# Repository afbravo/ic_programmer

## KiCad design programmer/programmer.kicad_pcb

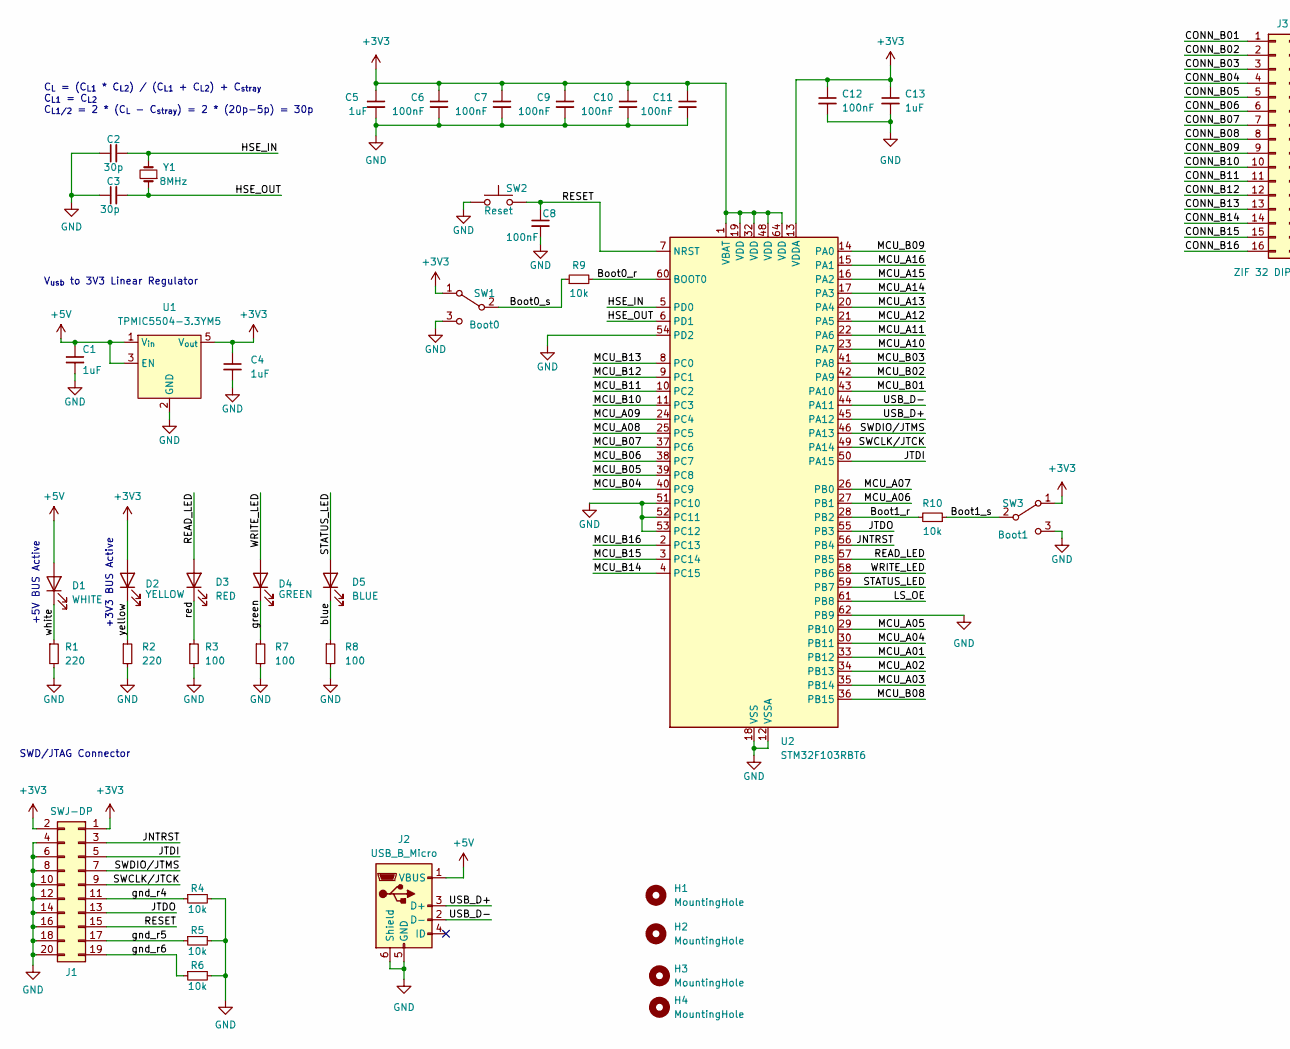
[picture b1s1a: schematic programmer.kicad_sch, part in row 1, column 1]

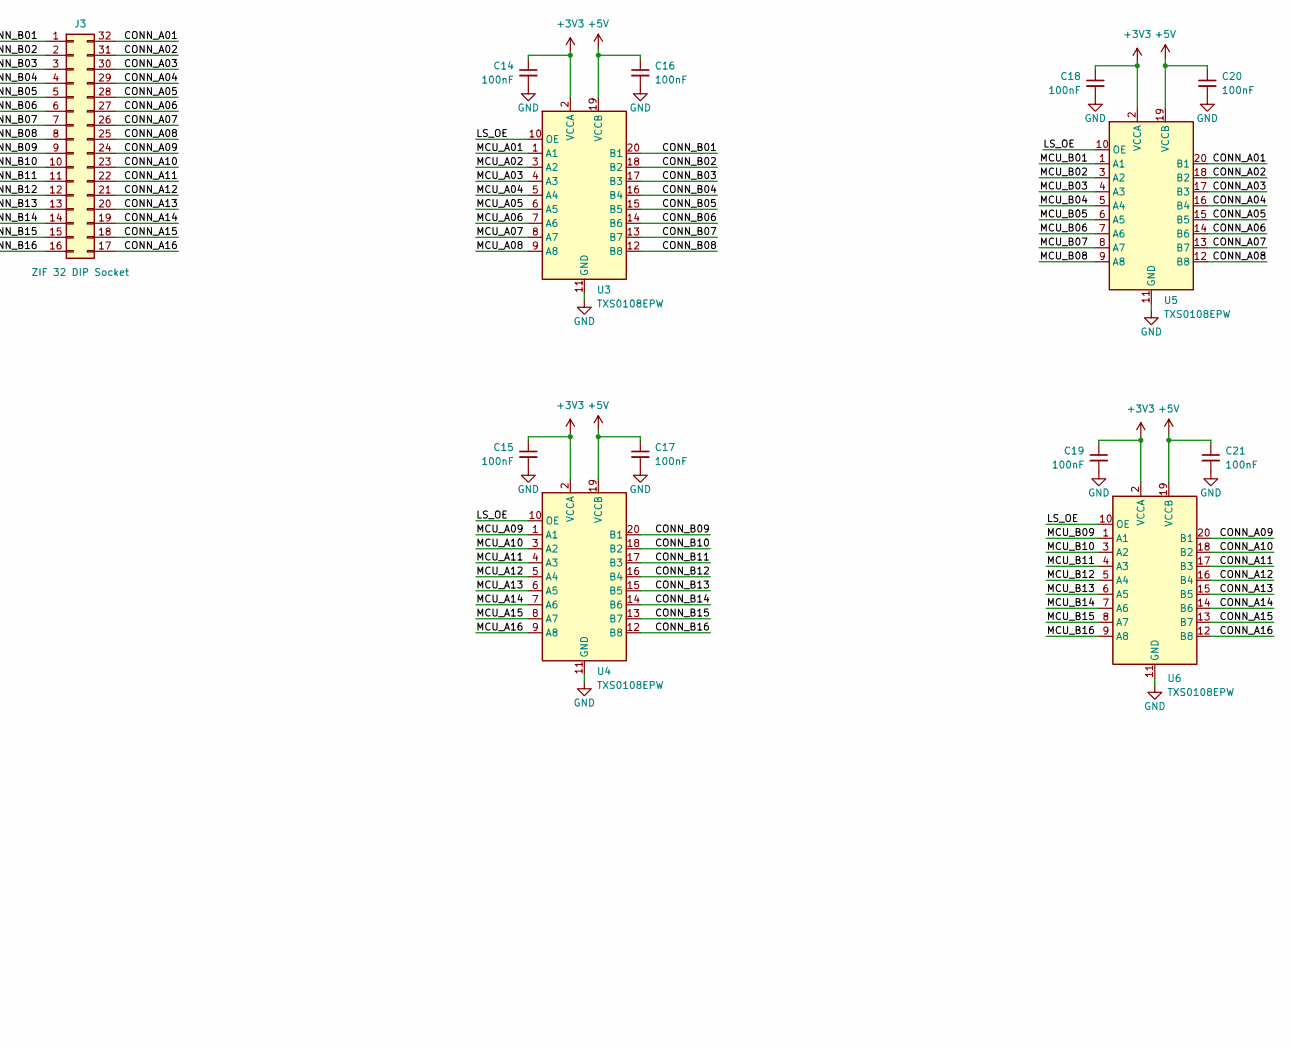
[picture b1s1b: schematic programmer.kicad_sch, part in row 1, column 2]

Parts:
C1, C4, C5, C13: 1uF; C_0603_1608Metric; LCSC C93816
C2, C3: 30p; C_0402_1005Metric; LCSC C525209
C6, C7, C8, C9, C10, C11, C12, C14, C15, C16, C17, C18, C19, C20, C21: 100nF; C_0402_1005Metric; LCSC C71629
D1: WHITE; LED_0805_2012Metric; LCSC C34499
D2: YELLOW; LED_0805_2012Metric; LCSC C434434
D3: RED; LED_0805_2012Metric; LCSC C84256
D4: GREEN; LED_0805_2012Metric; LCSC C2297
D5: BLUE; LED_0805_2012Metric; LCSC C84259
H1, H2, H3, H4: MountingHole; MountingHole_3.2mm_M3_Pad_Via
J1: SWJ-DP; PinHeader_2x10_P2.54mm_Vertical; LCSC C3405
J2: USB_B_Micro; USB_Micro-B_XKB_U254-051T-4BH83-F1S; LCSC C2682229
J3: ZIF 32 DIP Socket; DIP_Socket-32_W11.9_W12.7_W15.24_W17.78_W18.5_3M_232-1285-0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
R1, R2: 220; R_0402_1005Metric; LCSC C102898
R3, R7, R8: 100; R_0402_1005Metric; LCSC C106233
R4, R5, R6, R9, R10: 10k; R_0603_1608Metric; LCSC C190610
SW1: Boot0; SW_SWDT_SMD_0.8x1.4_0.8x2; LCSC C319019
SW2: Reset; SW_SMD_1.8x1.35_4.15; LCSC C720477
SW3: Boot1; SW_SWDT_SMD_0.8x1.4_0.8x2; LCSC C319019
U1: TPMIC5504-3.3YM5; SOT-23-5; LCSC C3021093
U2: STM32F103RBT6; LQFP-64_10x10mm_P0.5mm; LCSC C8735
U3, U4, U5, U6: TXS0108EPW; TSSOP-20_4.4x6.5mm_P0.65mm
Y1: 8MHz; Crystal_SMD_5032-2Pin_5.0x3.2mm; LCSC C115962

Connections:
+3V3: C4.1, C5.1, C6.1, C7.1, C9.1, C10.1, C11.1, C12.1, C13.1, C14.1, C15.1, C18.1, C19.1, D2.2 (A), J1.1, J1.2, SW1.1 (A), SW3.1 (A), U1.5 (V_{out}), U2.1 (VBAT), U2.13 (VDDA), U2.19 (VDD), U2.32 (VDD), U2.48 (VDD), U2.64 (VDD), U3.2 (VCCA), U4.2 (VCCA), U5.2 (VCCA), U6.2 (VCCA)
+5V: C1.1, C16.1, C17.1, C20.1, C21.1, D1.2 (A), J2.1 (VBUS), U1.1 (V_{in}), U1.3 (EN), U3.19 (VCCB), U4.19 (VCCB), U5.19 (VCCB), U6.19 (VCCB)
/Boot0_r: R9.2, U2.60 (BOOT0)
/Boot0_s: R9.1, SW1.2 (B)
/Boot1_r: R10.2, U2.28 (PB2)
/Boot1_s: R10.1, SW3.2 (B)
/CONN_A01: J3.32, U5.20 (B1)
/CONN_A02: J3.31, U5.18 (B2)
/CONN_A03: J3.30, U5.17 (B3)
/CONN_A04: J3.29, U5.16 (B4)
/CONN_A05: J3.28, U5.15 (B5)
/CONN_A06: J3.27, U5.14 (B6)
/CONN_A07: J3.26, U5.13 (B7)
/CONN_A08: J3.25, U5.12 (B8)
/CONN_A09: J3.24, U6.20 (B1)
/CONN_A10: J3.23, U6.18 (B2)
/CONN_A11: J3.22, U6.17 (B3)
/CONN_A12: J3.21, U6.16 (B4)
/CONN_A13: J3.20, U6.15 (B5)
/CONN_A14: J3.19, U6.14 (B6)
/CONN_A15: J3.18, U6.13 (B7)
/CONN_A16: J3.17, U6.12 (B8)
/CONN_B01: J3.1, U3.20 (B1)
/CONN_B02: J3.2, U3.18 (B2)
/CONN_B03: J3.3, U3.17 (B3)
/CONN_B04: J3.4, U3.16 (B4)
/CONN_B05: J3.5, U3.15 (B5)
/CONN_B06: J3.6, U3.14 (B6)
/CONN_B07: J3.7, U3.13 (B7)
/CONN_B08: J3.8, U3.12 (B8)
/CONN_B09: J3.9, U4.20 (B1)
/CONN_B10: J3.10, U4.18 (B2)
/CONN_B11: J3.11, U4.17 (B3)
/CONN_B12: J3.12, U4.16 (B4)
/CONN_B13: J3.13, U4.15 (B5)
/CONN_B14: J3.14, U4.14 (B6)
/CONN_B15: J3.15, U4.13 (B7)
/CONN_B16: J3.16, U4.12 (B8)
/HSE_IN: C2.2, U2.5 (PD0), Y1.2
/HSE_OUT: C3.2, U2.6 (PD1), Y1.1
/JNTRST: J1.3, U2.56 (PB4)
/JTDI: J1.5, U2.50 (PA15)
/JTDO: J1.13, U2.55 (PB3)
/LS_OE: U2.61 (PB8), U3.10 (OE), U4.10 (OE), U5.10 (OE), U6.10 (OE)
/MCU_A01: U2.33 (PB12), U3.1 (A1)
/MCU_A02: U2.34 (PB13), U3.3 (A2)
/MCU_A03: U2.35 (PB14), U3.4 (A3)
/MCU_A04: U2.30 (PB11), U3.5 (A4)
/MCU_A05: U2.29 (PB10), U3.6 (A5)
/MCU_A06: U2.27 (PB1), U3.7 (A6)
/MCU_A07: U2.26 (PB0), U3.8 (A7)
/MCU_A08: U2.25 (PC5), U3.9 (A8)
/MCU_A09: U2.24 (PC4), U4.1 (A1)
/MCU_A10: U2.23 (PA7), U4.3 (A2)
/MCU_A11: U2.22 (PA6), U4.4 (A3)
/MCU_A12: U2.21 (PA5), U4.5 (A4)
/MCU_A13: U2.20 (PA4), U4.6 (A5)
/MCU_A14: U2.17 (PA3), U4.7 (A6)
/MCU_A15: U2.16 (PA2), U4.8 (A7)
/MCU_A16: U2.15 (PA1), U4.9 (A8)
/MCU_B01: U2.43 (PA10), U5.1 (A1)
/MCU_B02: U2.42 (PA9), U5.3 (A2)
/MCU_B03: U2.41 (PA8), U5.4 (A3)
/MCU_B04: U2.40 (PC9), U5.5 (A4)
/MCU_B05: U2.39 (PC8), U5.6 (A5)
/MCU_B06: U2.38 (PC7), U5.7 (A6)
/MCU_B07: U2.37 (PC6), U5.8 (A7)
/MCU_B08: U2.36 (PB15), U5.9 (A8)
/MCU_B09: U2.14 (PA0), U6.1 (A1)
/MCU_B10: U2.11 (PC3), U6.3 (A2)
/MCU_B11: U2.10 (PC2), U6.4 (A3)
/MCU_B12: U2.9 (PC1), U6.5 (A4)
/MCU_B13: U2.8 (PC0), U6.6 (A5)
/MCU_B14: U2.4 (PC15), U6.7 (A6)
/MCU_B15: U2.3 (PC14), U6.8 (A7)
/MCU_B16: U2.2 (PC13), U6.9 (A8)
/READ_LED: D3.2 (A), U2.57 (PB5)
/RESET: C8.1, J1.15, SW2.2, U2.7 (NRST)
/STATUS_LED: D5.2 (A), U2.59 (PB7)
/SWCLK/JTCK: J1.9, U2.49 (PA14)
/SWDIO/JTMS: J1.7, U2.46 (PA13)
/USB_D+: J2.3 (D+), U2.45 (PA12)
/USB_D-: J2.2 (D-), U2.44 (PA11)
/WRITE_LED: D4.2 (A), U2.58 (PB6)
/blue: D5.1 (K), R8.1
/gnd_r4: J1.11, R4.1
/gnd_r5: J1.17, R5.1
/gnd_r6: J1.19, R6.1
/green: D4.1 (K), R7.1
/red: D3.1 (K), R3.1
/white: D1.1 (K), R1.1
/yellow: D2.1 (K), R2.1
GND: C1.2, C2.1, C3.1, C4.2, C5.2, C6.2, C7.2, C8.2, C9.2, C10.2, C11.2, C12.2, C13.2, C14.2, C15.2, C16.2, C17.2, C18.2, C19.2, C20.2, C21.2, J1.4, J1.6, J1.8, J1.10, J1.12, J1.14, J1.16, J1.18, J1.20, J2.5 (GND), J2.6 (Shield), R1.2, R2.2, R3.2, R4.2, R5.2, R6.2, R7.2, R8.2, SW1.3 (C), SW2.1, SW3.3 (C), U1.2 (GND), U2.12 (VSSA), U2.18 (VSS), U2.31 (VSS), U2.47 (VSS), U2.51 (PC10), U2.52 (PC11), U2.53 (PC12), U2.54 (PD2), U2.62 (PB9), U2.63 (VSS), U3.11 (GND), U4.11 (GND), U5.11 (GND), U6.11 (GND)

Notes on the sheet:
V_{usb} to 3V3 Linear Regulator
+5V BUS Active
C_{L} = (C_{L1} * C_{L2}) / (C_{L1} + C_{L2}) + C_{stray} C_{L1} = C_{L2} C_{L1/2} = 2 * (C_{L} - C_{stray}) = 2 * (20p-5p) = 30p
+3V3 BUS Active
SWD/JTAG Connector

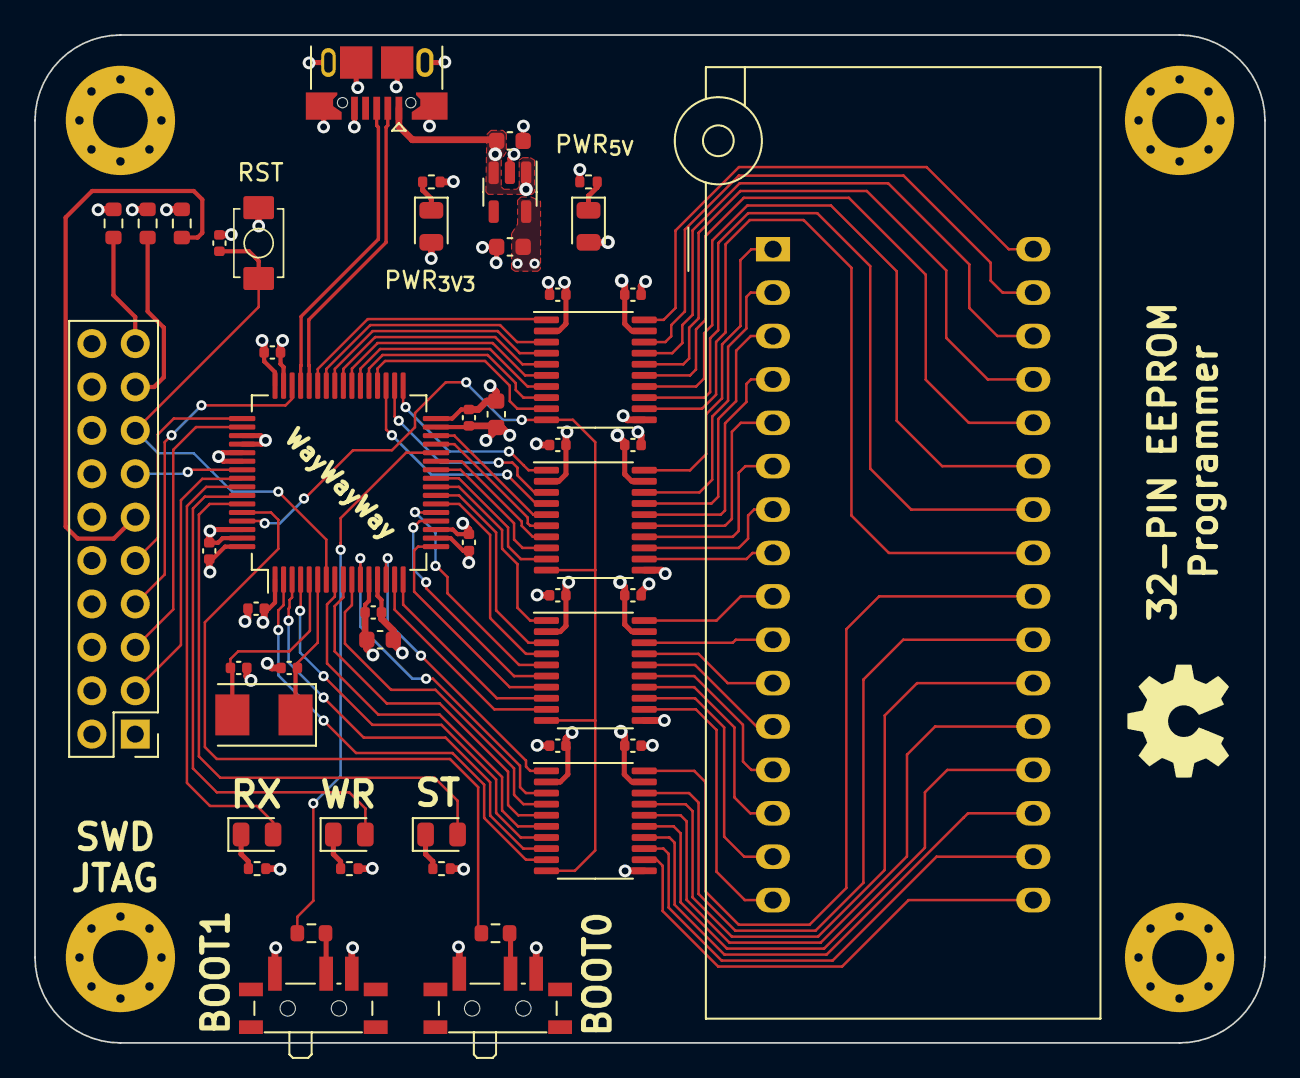
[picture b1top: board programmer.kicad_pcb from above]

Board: 4 copper layers, 72.0 x 59.0 mm, 53 parts (0 on the bottom side), 93 nets.

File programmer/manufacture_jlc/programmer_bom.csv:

Designator,Val,Package,Mid X,Mid Y,Rotation,Layer
C1,1uF,C_0603_1608Metric,138.707500,-78.620000,0.000000,top
C2,30p,C_0402_1005Metric,122.827500,-109.470000,180.000000,top
C3,30p,C_0402_1005Metric,125.787500,-109.470000,0.000000,top
C4,1uF,C_0603_1608Metric,138.707500,-84.820000,180.000000,top
C5,1uF,C_0603_1608Metric,137.907500,-94.620000,-90.000000,top
C6,100nF,C_0402_1005Metric,124.800000,-91.000000,0.000000,top
C7,100nF,C_0402_1005Metric,123.850000,-106.000000,180.000000,top
C8,100nF,C_0402_1005Metric,121.700000,-84.600000,90.000000,top
C9,100nF,C_0402_1005Metric,136.307500,-94.820000,-90.000000,top
C10,100nF,C_0402_1005Metric,121.107500,-102.620000,90.000000,top
C11,100nF,C_0402_1005Metric,136.307500,-102.120000,-90.000000,top
C12,100nF,C_0402_1005Metric,130.707500,-106.220000,180.000000,top
C13,1uF,C_0603_1608Metric,131.107500,-107.820000,180.000000,top
C14,100nF,C_0402_1005Metric,141.507500,-96.420000,180.000000,top
C15,100nF,C_0402_1005Metric,141.507500,-105.220000,180.000000,top
C16,100nF,C_0402_1005Metric,145.907500,-96.420000,0.000000,top
C17,100nF,C_0402_1005Metric,145.907500,-105.220000,0.000000,top
C18,100nF,C_0402_1005Metric,141.507500,-87.620000,180.000000,top
C19,100nF,C_0402_1005Metric,141.507500,-114.020000,180.000000,top
C20,100nF,C_0402_1005Metric,145.907500,-87.620000,0.000000,top
C21,100nF,C_0402_1005Metric,145.907500,-114.020000,0.000000,top
D1,WHITE,LED_0805_2012Metric,143.307500,-83.620000,-90.000000,top
D2,YELLOW,LED_0805_2012Metric,134.107500,-83.620000,-90.000000,top
D3,RED,LED_0805_2012Metric,123.907500,-119.220000,0.000000,top
D4,GREEN,LED_0805_2012Metric,129.307500,-119.220000,0.000000,top
D5,BLUE,LED_0805_2012Metric,134.707500,-119.220000,0.000000,top
J1,SWJ-DP,PinHeader_2x10_P2.54mm_Vertical,116.775000,-113.345000,180.000000,top
J2,USB_B_Micro,USB_Micro-B_XKB_U254-051T-4BH83-F1S,130.907500,-74.420000,180.000000,top
J3,ZIF 32 DIP Socket,DIP_Socket-32_W11.9_W12.7_W15.24_W17.78_W18.5_3M_232-1285-00-0602J,154.107500,-84.960000,0.000000,top
R1,220,R_0402_1005Metric,143.307500,-81.020000,180.000000,top
R2,220,R_0402_1005Metric,134.107500,-81.020000,0.000000,top
R3,100,R_0402_1005Metric,123.907500,-121.220000,0.000000,top
R4,10k,R_0603_1608Metric,119.500000,-83.450000,90.000000,top
R5,10k,R_0603_1608Metric,117.500000,-83.450000,90.000000,top
R6,10k,R_0603_1608Metric,115.500000,-83.450000,90.000000,top
R7,100,R_0402_1005Metric,129.307500,-121.220000,0.000000,top
R8,100,R_0402_1005Metric,134.707500,-121.220000,0.000000,top
R9,10k,R_0603_1608Metric,137.862500,-125.000000,180.000000,top
R10,10k,R_0603_1608Metric,127.087500,-125.000000,180.000000,top
SW1,Boot0,SW_SWDT_SMD_0.8x1.4_0.8x2,137.995000,-129.400000,0.000000,top
SW2,Reset,SW_SMD_1.8x1.35_4.15,124.000000,-84.600000,90.000000,top
SW3,Boot1,SW_SWDT_SMD_0.8x1.4_0.8x2,127.200000,-129.400000,0.000000,top
U1,TPMIC5504-3.3YM5,SOT-23-5,138.707500,-81.620000,-90.000000,top
U2,STM32F103RBT6,LQFP-64_10x10mm_P0.5mm,128.707500,-98.620000,90.000000,top
U3,TXS0108EPW,TSSOP-20_4.4x6.5mm_P0.65mm,143.707500,-100.820000,0.000000,top
U4,TXS0108EPW,TSSOP-20_4.4x6.5mm_P0.65mm,143.707500,-109.620000,0.000000,top
U5,TXS0108EPW,TSSOP-20_4.4x6.5mm_P0.65mm,143.707500,-92.020000,0.000000,top
U6,TXS0108EPW,TSSOP-20_4.4x6.5mm_P0.65mm,143.707500,-118.420000,0.000000,top
Y1,8MHz,Crystal_SMD_5032-2Pin_5.0x3.2mm,124.307500,-112.220000,180.000000,top
